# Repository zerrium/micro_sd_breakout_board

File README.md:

# Micro SD Breakout Board
A simple Micro SD breakout board designed using KiCad<br>
Designed with KiCad 9<br>
[Micro SD card tray](https://www.mouser.com/ProductDetail/Same-Sky/MSD-1-A?qs=Z%252BL2brAPG1Ip18XLC4tUPQ%3D%3D)<br><br>
### Schematic

### PCB

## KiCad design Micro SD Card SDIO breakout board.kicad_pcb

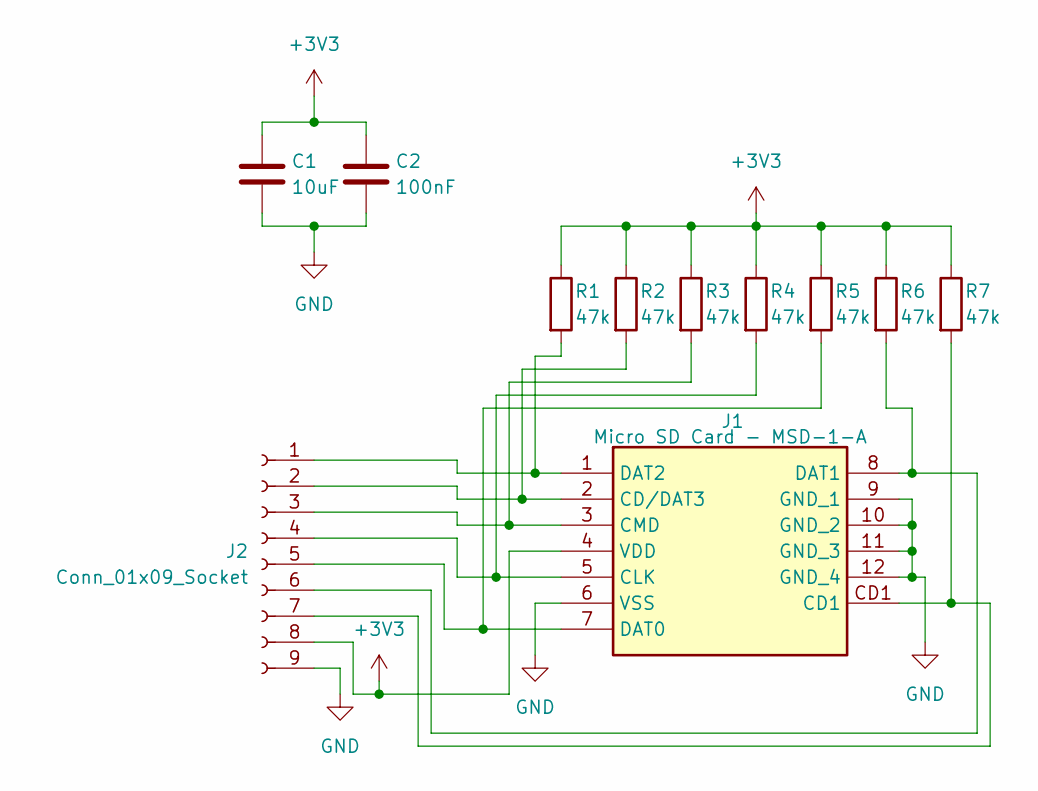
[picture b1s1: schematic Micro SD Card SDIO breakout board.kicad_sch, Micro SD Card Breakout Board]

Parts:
C1: 10uF; C_1206_3216Metric_Pad1.33x1.80mm_HandSolder
C2: 100nF; C_1206_3216Metric_Pad1.33x1.80mm_HandSolder
J1: Micro SD Card - MSD-1-A; Micro SD Card - MSD1A; Mouser Part Number 179-MSD-1-A
J2: Conn_01x09_Socket; PinHeader_1x09_P2.54mm_Vertical
R1, R2, R3, R4, R5, R6, R7: 47k; R_1206_3216Metric_Pad1.30x1.75mm_HandSolder

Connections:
+3V3: C1.1, C2.1, J1.4 (VDD), J2.8, R1.1, R2.1, R3.1, R4.1, R5.1, R6.1, R7.1
GND: C1.2, C2.2, J1.6 (VSS), J1.9 (GND_1), J1.10 (GND_2), J1.11 (GND_3), J1.12 (GND_4), J2.9
unnamed: J1.2 (CD/DAT3), J2.2, R2.2
unnamed: J1.5 (CLK), J2.4, R4.2
unnamed: J1.3 (CMD), J2.3, R3.2
unnamed: J1.7 (DAT0), J2.5, R5.2
unnamed: J1.8 (DAT1), J2.6, R6.2
unnamed: J1.1 (DAT2), J2.1, R1.2
unnamed: J1.CD1, J2.7, R7.2

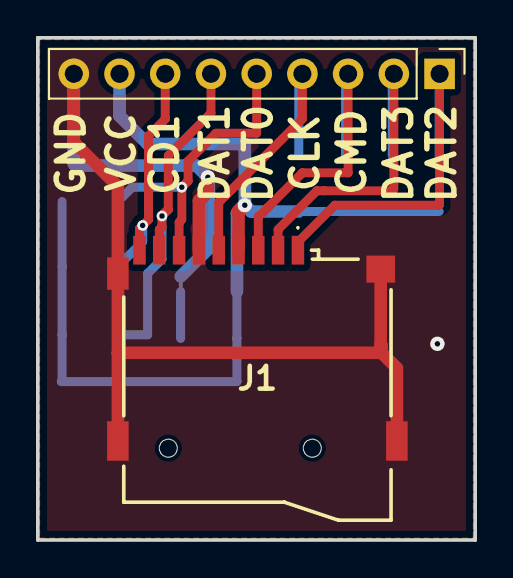
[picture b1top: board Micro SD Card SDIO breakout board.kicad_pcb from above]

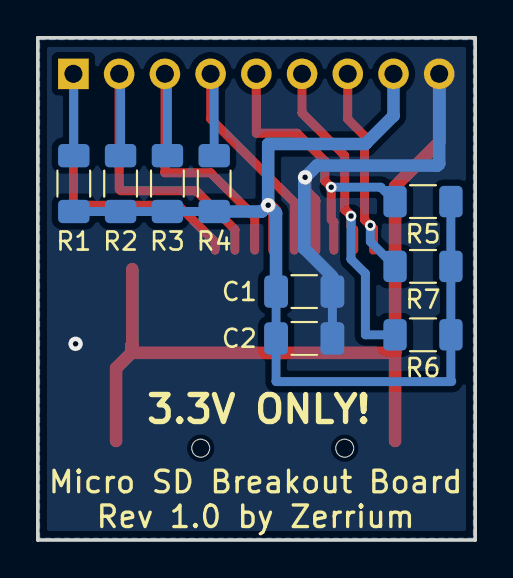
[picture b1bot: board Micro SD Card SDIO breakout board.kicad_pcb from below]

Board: 2 copper layers, 24.3 x 27.9 mm, 11 parts (9 on the bottom side), 9 nets.

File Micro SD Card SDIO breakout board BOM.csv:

"Id";"Designator";"Footprint";"Quantity";"Designation";"Supplier and ref";
1;"J2";"PinHeader_1x09_P2.54mm_Vertical";1;" ";;;
2;"J1";"Micro SD Card - MSD1A";1;"Micro SD Card - MSD-1-A";;;
3;"C2";"C_1206_3216Metric_Pad1.33x1.80mm_HandSolder";1;"100nF";;;
4;"R3,R6,R4,R5,R2,R1,R7";"R_1206_3216Metric_Pad1.30x1.75mm_HandSolder";7;"47k";;;
5;"C1";"C_1206_3216Metric_Pad1.33x1.80mm_HandSolder";1;"10uF";;;
